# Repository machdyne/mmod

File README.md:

# MMOD

## Overview

MMOD is a 3.3V SPI memory module used in Machdyne / Lone Dynamics computers in order to allow for user-replaceable and user-upgradeable memory. The module is inserted into the MMOD socket with the top-side components facing the host board.

MMOD modules are compatible with Pmod&trade; Interface Type 2 (SPI) and can be used in 6 or 12 pin Pmod&trade; sockets, but Pmod modules are not necessarily compatible with MMOD sockets due to differences in size and requirements.

This repo contains specifications, pinouts, footprints, schematics and PCB layouts.

Find more information on the [MMOD product page](https://machdyne.com/product/mmod/).

## Pinout

| Pin | Signal |
| --- | ------ |
| 1 | SS |
| 2 | MOSI |
| 3 | MISO |
| 4 | SCK |
| 5 | GND |
| 6 | PWR3V3 |

## Dimensions

Width: 16.5mm (parallel with header)

Length: 12.5mm max (perpendicular to header)

Height: 8mm max (top of header to top of bottom-side components)

## MMOD Board Requirements

- The top-side components must not touch the host board.
- The module must not interfere with the SPI bus unless SS is asserted (low).
- The module should provide decoupling capacitors for the memory.
- The module should provide any necessary pull-up/down resistors for the memory.
- SPI SS should be pulled high with a 10K resistor.
- SPI MOSI, MISO and SCK should have no pull-up/down resistors.
- The module must not draw more than 50mA current at any time.

## MMOD-D (Type-D) Additional Requirements

MMOD-D is a special type of MMOD containing two SPI devices, the requirements are the same as MMOD but with the following differences:

- The SPI bus is expected to be dedicated to the MMOD.
- The module may interfere with the SPI bus regardless of the state of SS.

## License

The contents of this repo are released under the [Lone Dynamics Open License](LICENSE.md) with the following exceptions:

- The KiCad design files contain parts of the [kicad-pmod](https://github.com/mithro/kicad-pmod) library which is released under the [Apache License, Version 2.0](https://www.apache.org/licenses/LICENSE-2.0.html).

Note: You can use these designs for commercial purposes but we ask that instead of producing exact clones, that you either replace our trademarks and logos with your own or add your own next to ours.

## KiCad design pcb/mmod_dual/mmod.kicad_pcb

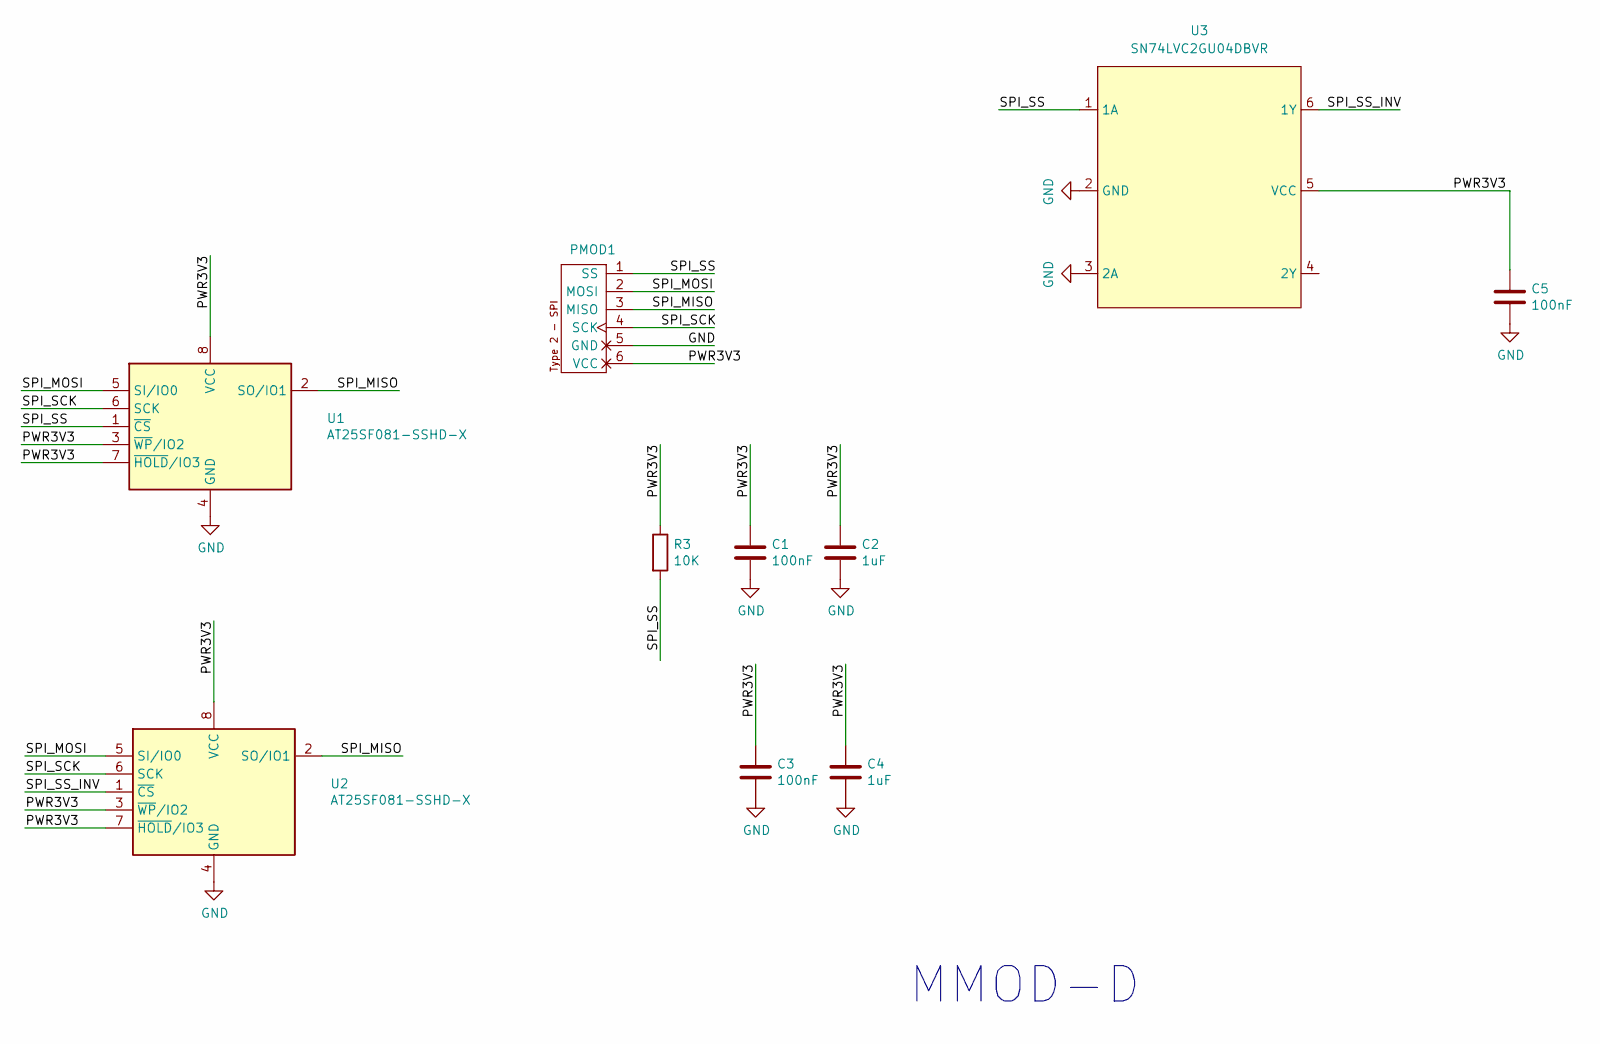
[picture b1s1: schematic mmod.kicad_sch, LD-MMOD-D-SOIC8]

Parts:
C1, C3: 100nF; C_0402_1005Metric
C2, C4: 1uF; C_0402_1005Metric
C5: 100nF; C_0402_1005Metric_Pad0.74x0.62mm_HandSolder
PMOD1: PMOD-Device-x1-Type-2-SPI; PinHeader_1x06_P2.54mm_Horizontal
R3: 10K; R_0402_1005Metric
U1, U2: AT25SF081-SSHD-X; SOIC-8_3.9x4.9mm_P1.27mm
U3: SN74LVC2GU04DBVR; SOT-23-6_Handsoldering

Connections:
/PWR3V3: C1.1, C2.1, C3.1, C4.1, C5.1, PMOD1.6 (VCC), R3.1, U1.3 (~WP/IO2), U1.7 (~HOLD/IO3), U1.8 (VCC), U2.3 (~WP/IO2), U2.7 (~HOLD/IO3), U2.8 (VCC), U3.5 (VCC)
/SPI_MISO: PMOD1.3 (MISO), U1.2 (SO/IO1), U2.2 (SO/IO1)
/SPI_MOSI: PMOD1.2 (MOSI), U1.5 (SI/IO0), U2.5 (SI/IO0)
/SPI_SCK: PMOD1.4 (SCK), U1.6 (SCK), U2.6 (SCK)
/SPI_SS: PMOD1.1 (SS), R3.2, U1.1 (~CS), U3.1 (1A)
/SPI_SS_INV: U2.1 (~CS), U3.6 (1Y)
GND: C1.2, C2.2, C3.2, C4.2, C5.2, PMOD1.5 (GND), U1.4 (GND), U2.4 (GND), U3.2 (GND), U3.3 (2A)

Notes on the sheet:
MMOD-D

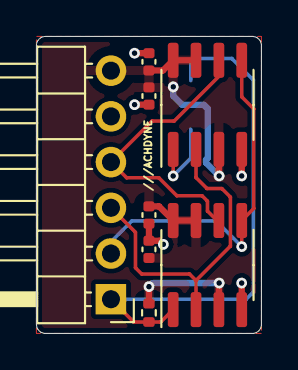
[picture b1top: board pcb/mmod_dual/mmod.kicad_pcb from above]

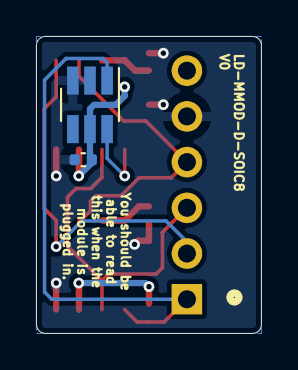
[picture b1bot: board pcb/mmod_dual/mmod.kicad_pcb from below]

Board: 2 copper layers, 12.5 x 16.5 mm, 10 parts (2 on the bottom side), 7 nets.

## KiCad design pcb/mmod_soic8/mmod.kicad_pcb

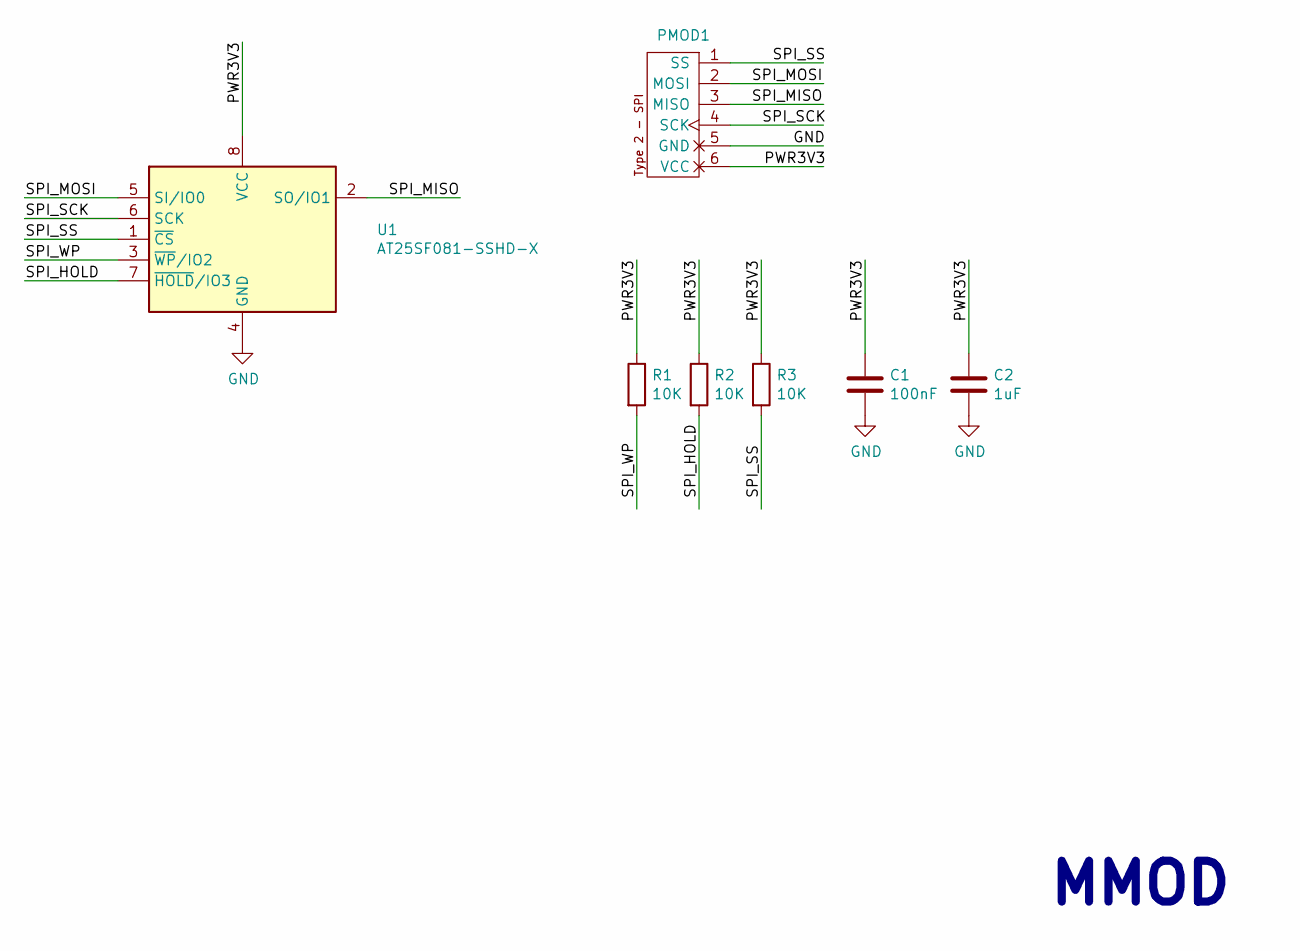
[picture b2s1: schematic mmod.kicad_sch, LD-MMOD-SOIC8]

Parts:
C1: 100nF; C_0603_1608Metric
C2: 1uF; C_0603_1608Metric
PMOD1: PMOD-Device-x1-Type-2-SPI; PinHeader_1x06_P2.54mm_Horizontal
R1, R2, R3: 10K; R_0603_1608Metric
U1: AT25SF081-SSHD-X; SOIC-8_3.9x4.9mm_P1.27mm

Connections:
/PWR3V3: C1.1, C2.1, PMOD1.6 (VCC), R1.1, R2.1, R3.1, U1.8 (VCC)
/SPI_HOLD: R2.2, U1.7 (~HOLD/IO3)
/SPI_MISO: PMOD1.3 (MISO), U1.2 (SO/IO1)
/SPI_MOSI: PMOD1.2 (MOSI), U1.5 (SI/IO0)
/SPI_SCK: PMOD1.4 (SCK), U1.6 (SCK)
/SPI_SS: PMOD1.1 (SS), R3.2, U1.1 (~CS)
/SPI_WP: R1.2, U1.3 (~WP/IO2)
GND: C1.2, C2.2, PMOD1.5 (GND), U1.4 (GND)

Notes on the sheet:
MMOD

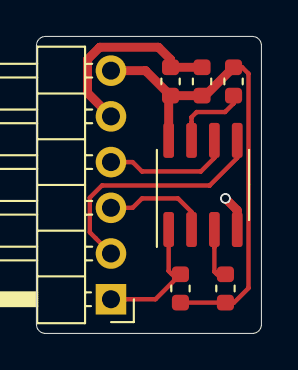
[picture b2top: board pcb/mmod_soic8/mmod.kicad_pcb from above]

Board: 2 copper layers, 12.5 x 16.5 mm, 7 parts (0 on the bottom side), 8 nets.

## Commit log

2022-02-22 add image to readme
2023-04-15 add pcb layouts
2023-11-13 add soic8 wide
2024-02-08 add MMOD-D
2024-02-08 add MMOD-D pcb layout

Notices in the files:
pcb/mmod_dual/mmod.kicad_sch:
Copyright © 2024 Lone Dynamics Corporation
pcb/mmod_soic8/mmod.kicad_sch:
Copyright © 2022 Lone Dynamics Corporation
pcb/mmod_soic8w/mmod.kicad_sch:
Copyright © 2023 Lone Dynamics Corporation
